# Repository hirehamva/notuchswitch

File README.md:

# No-Touch Door and Light Switch

A compact ATtiny3216 controller that switches one LED lamp by hand gesture or
when a sliding door moves in front of an APDS-9960 sensor. The repository
contains the KiCad design, parts list, PCB fabrication files, firmware, and the
documents needed to assemble and program the prototype.

## Prototype

*Controller PCB fitted in the enclosure with its cover removed.*

*Enclosure interior showing the power supply and wiring.*

*Front cover with separate sensor and status LED openings.*

## Build and program

1. Open `hardware/notuchswitch.kicad_pro` in KiCad 9 or later. PCB component
   placement is fixed; use the supplied Gerbers to order the board.
2. Assemble the board using [`hardware/BOM.csv`](hardware/BOM.csv) and the
   [hardware notes](hardware/README.md). Confirm the parts marked for footprint
   verification before ordering or soldering.
3. Open `software/notuchswitch_firmware/notuchswitch_firmware.ino` in Arduino
   IDE 2. Install megaTinyCore and select the ATtiny3216 settings described in
   [`software/README.md`](software/README.md).
4. Program through the on-board J7 SerialUPDI header using a 3.3 V USB-to-UART
   adapter. The classic USBasp programmer does not connect directly to J7; see
   [`software/SERIALUPDI.md`](software/SERIALUPDI.md).
5. Print the [cover drilling template](hardware/templates/cover_drill_template.pdf)
   at 100% and verify its 20 mm scale bar before drilling.

See the [user guide](docs/user-guide.md) for operation, menu settings, and
calibration.

## Safety and license

This is a mains-powered engineering prototype, not a certified product. Verify
the exact components, insulation distances, enclosure, wiring, temperature,
and applicable electrical safety requirements before connecting it to mains.

The project is released under the MIT License; see [`LICENSE`](LICENSE).

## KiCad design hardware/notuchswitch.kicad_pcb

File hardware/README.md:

# Hardware Assembly

Open `notuchswitch.kicad_pro` in KiCad 9 or later. The PCB placement and
outline are fixed to fit the selected enclosure; do not move components.

## Required files

- `notuchswitch.kicad_sch`, `notuchswitch.kicad_pcb`, and
  `notuchswitch.kicad_pro`: schematic, PCB, and project.
- `BOM.csv`: component values, footprints, and parts that still need a
  dimensional check.
- `fabrication/gerber/`: copper, mask, silkscreen, outline, and drill files
  for PCB fabrication.
- `notuchswitch.pretty/`, `notuchswitch.kicad_sym`, `fp-lib-table`, and
  `sym-lib-table`: project-local footprints and symbol library configuration.
- `templates/cover_drill_template.pdf`: printable sensor and LED hole layout.

## Assembly notes

1. Order the PCB from the supplied Gerber and drill files, or export fresh
   fabrication files from the reviewed KiCad project.
2. Populate components according to `BOM.csv`. The fuse, varistor, and X2
   capacitor footprints are placeholders: verify the exact purchased parts,
   lead spacing, and body dimensions before soldering.
3. Confirm the APDS-9960 breakout pin order before inserting it. The board
   expects `VL, GND, VCC, SDA, SCL, INT`.
4. Solder the four marked 0.75 mm2 leads: brown `L_IN`, blue `N_IN`, black
   `L_SW`, and blue `N_OUT`. Keep the two neutral leads separately identified.
5. Relay pin 14 is brought out to solder pad `J8`. Connect it to fused live
   with an insulated external wire as shown by the schematic.
6. Do not tin stranded wire ends that will be clamped into screw terminals.
7. Mount the enclosure first, then fit the PCB. Print the cover template at
   100% and verify its 20 mm scale bar before drilling.

## Design details

- Two-layer, 1.0 mm FR4 PCB with a fixed octagonal outline.
- `HLK-2M05` isolated supply: 5 V, 400 mA continuous. Verify the load budget
  for the relay, LED, and the exact APDS breakout used.
- The recommended `10D561K` varistor may not match the supplied substitute;
  confirm its rating and dimensions against the supply manufacturer's data.
- Mains and low-voltage copper are separated by the project's 3 mm design rule.
- J7 is the on-board 2x2 SerialUPDI interface. R9 (470 ohm) and D5 (BAT54HT1G)
  are already fitted on the PCB design.
- USB-A provides 5 V only; D+ and D- are unconnected. Charging behavior is
  device-dependent and is not guaranteed.

The Gerber set is included as a fabrication artifact. Recheck the current KiCad
design, exact purchased components, and electrical safety before fabrication or
connecting mains. This prototype is not a certified product.

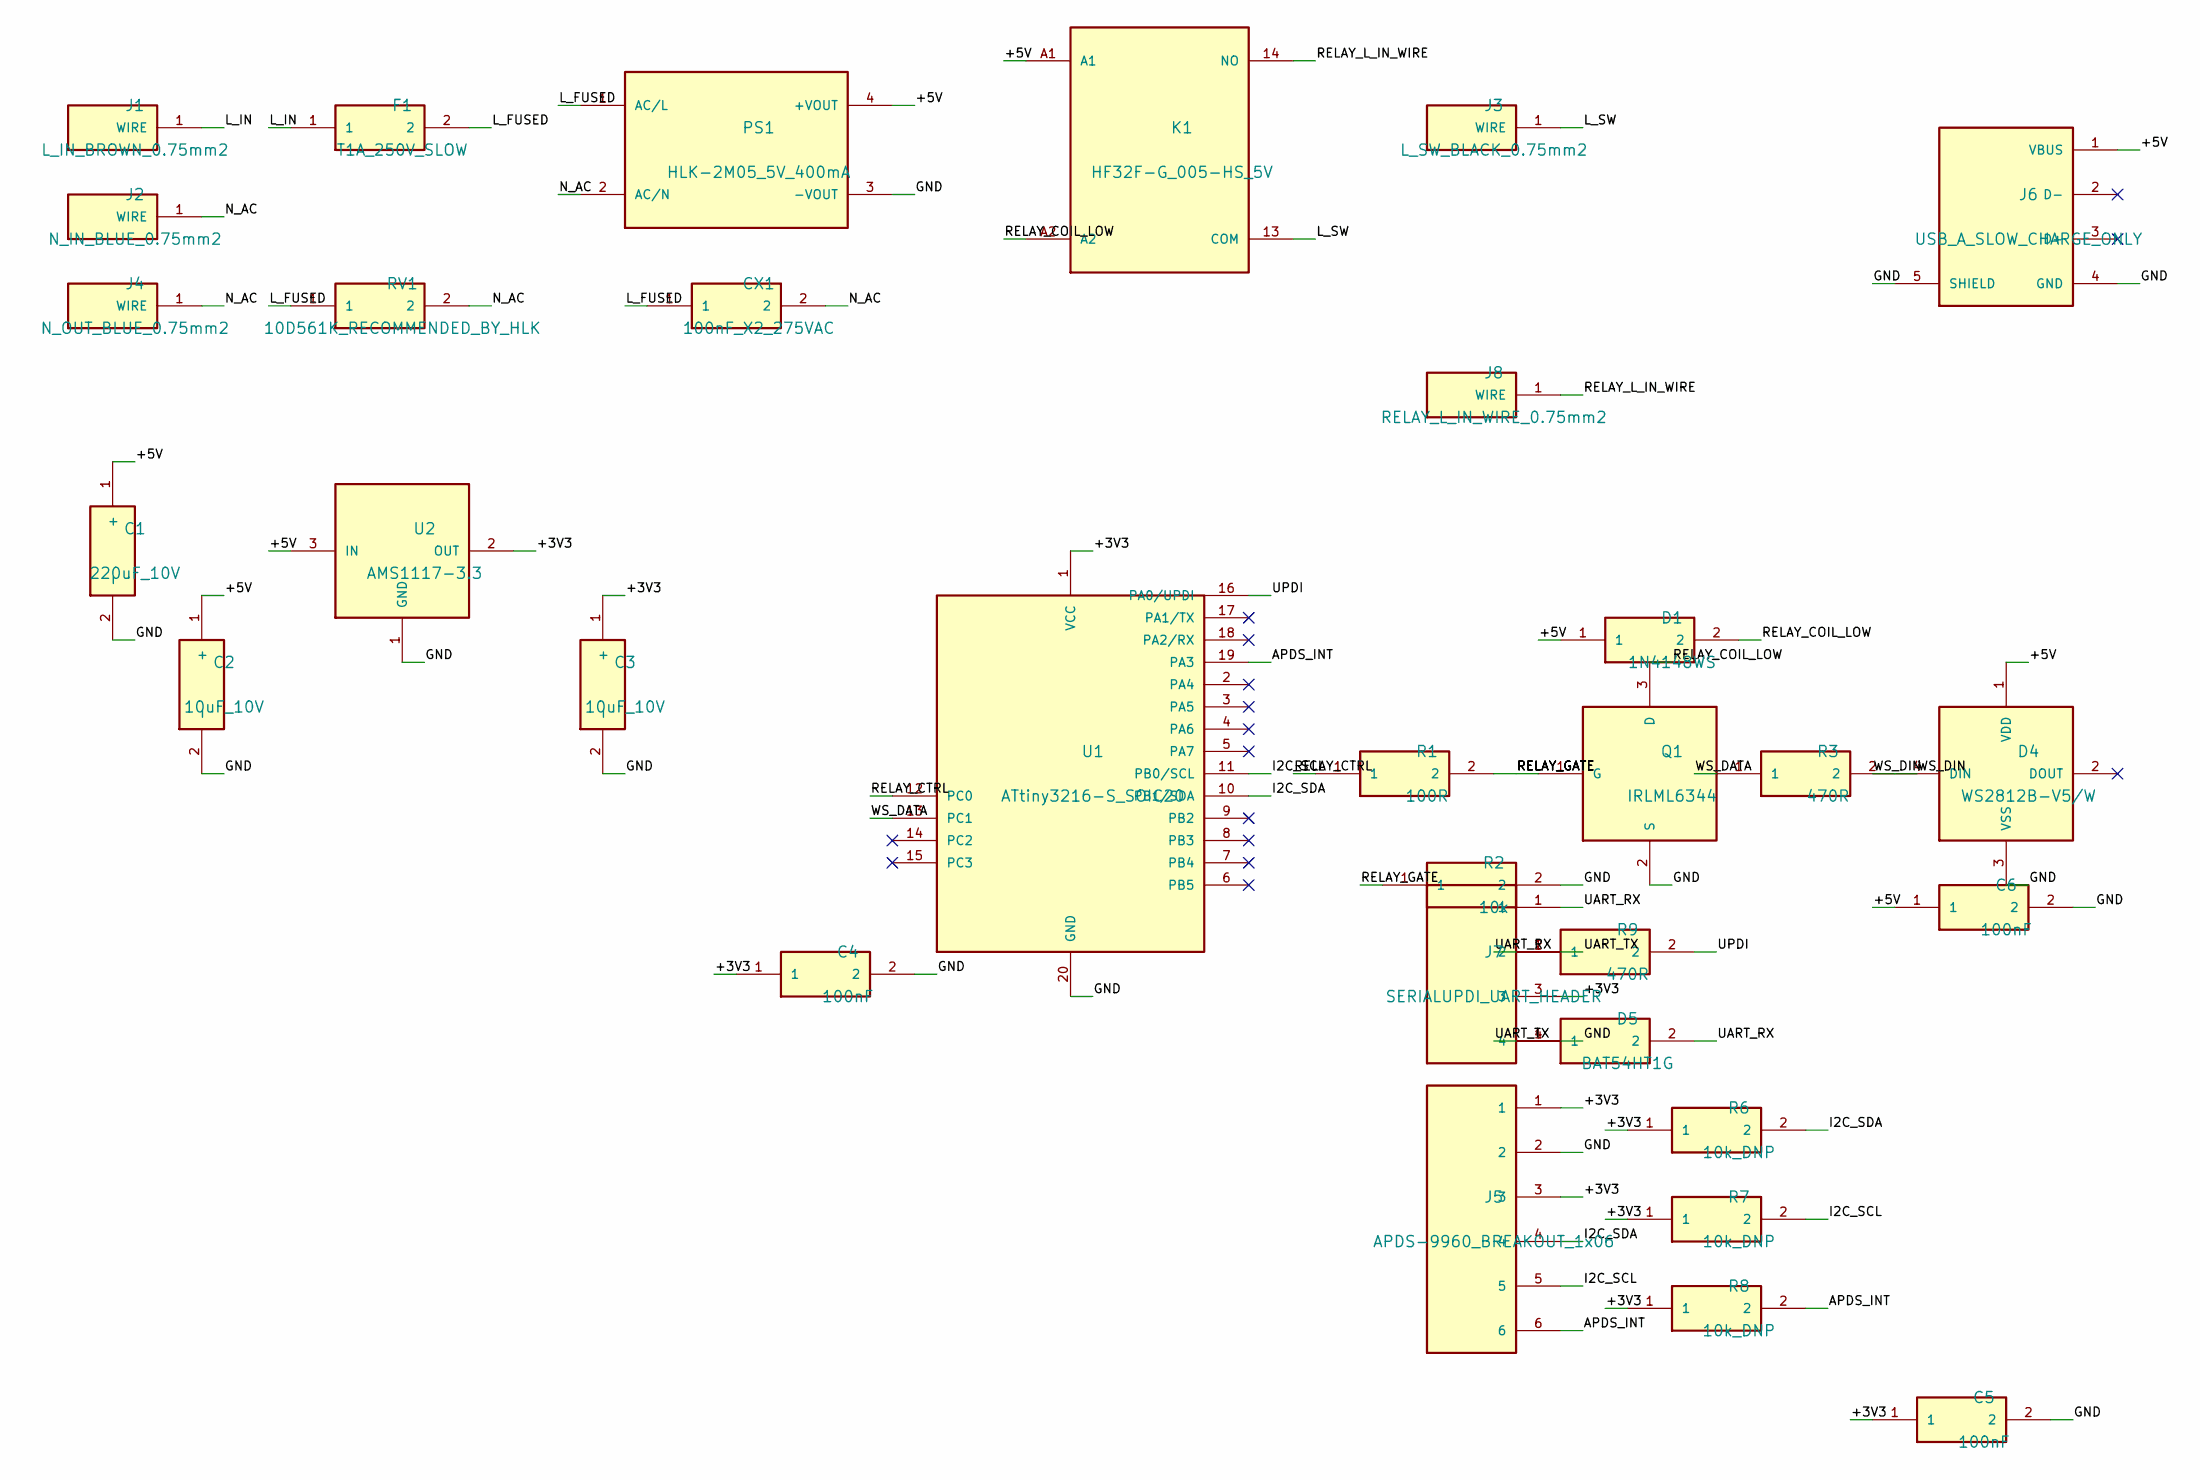
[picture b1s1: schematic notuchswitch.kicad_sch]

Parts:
C1: 220uF_10V; C_Radial_D6.3mm_H7.0mm_P2.50mm
C2, C3: 10uF_10V; C_Radial_D5.0mm_H5.0mm_P2.00mm
C4, C5, C6: 100nF; C_0805_2012Metric_Pad1.18x1.45mm_HandSolder
CX1: 100nF_X2_275VAC; X2_Capacitor_P10.00mm_PLACEHOLDER
D1: 1N4148WS; D_SOD-323_HandSoldering
D4: WS2812B-V5/W; LED_WS2812B_PLCC4_5.0x5.0mm_P3.2mm
D5: BAT54HT1G; D_SOD-323_HandSoldering
F1: T1A_250V_SLOW; Fuse_Radial_P5.08mm_PLACEHOLDER
J1: L_IN_BROWN_0.75mm2; WirePad_D3.2mm
J2: N_IN_BLUE_0.75mm2; WirePad_D3.2mm
J3: L_SW_BLACK_0.75mm2; WirePad_D3.2mm
J4: N_OUT_BLUE_0.75mm2; WirePad_D3.2mm
J5: APDS-9960_BREAKOUT_1x06; PinHeader_1x06_P2.54mm_Vertical
J6: USB_A_SLOW_CHARGE_ONLY; USB_A_Molex_67643_Horizontal
J7: SERIALUPDI_UART_HEADER; PinHeader_2x02_P2.54mm_Vertical
J8: RELAY_L_IN_WIRE_0.75mm2; WirePad_D3.2mm
K1: HF32F-G_005-HS_5V; HF32F-G
PS1: HLK-2M05_5V_400mA; HLK-2M05
Q1: IRLML6344; SOT-23
R1: 100R; R_0805_2012Metric_Pad1.20x1.40mm_HandSolder
R2: 10k; R_0805_2012Metric_Pad1.20x1.40mm_HandSolder
R3, R9: 470R; R_0805_2012Metric_Pad1.20x1.40mm_HandSolder
R6, R7, R8: 10k_DNP; R_0805_2012Metric_Pad1.20x1.40mm_HandSolder
RV1: 10D561K_RECOMMENDED_BY_HLK; Varistor_10D_P7.50mm_PLACEHOLDER
U1: ATtiny3216-S_SOIC20; SOIC-20W_7.5x12.8mm_P1.27mm
U2: AMS1117-3.3; SOT-223-3_TabPin2

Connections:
+3V3: C3.1 (+), C4.1, C5.1, J5.1, J5.3, J7.3, R6.1, R7.1, R8.1, U1.1 (VCC), U2.2 (OUT)
+5V: C1.1 (+), C2.1 (+), C6.1, D1.1, D4.1 (VDD), J6.1 (VBUS), K1.A1, PS1.4 (+VOUT), U2.3 (IN)
APDS_INT: J5.6, R8.2, U1.19 (PA3)
GND: C1.2 (-), C2.2 (-), C3.2 (-), C4.2, C5.2, C6.2, D4.3 (VSS), J5.2, J6.4 (GND), J6.5 (SHIELD), J7.4, PS1.3 (-VOUT), Q1.2 (S), R2.2, U1.20 (GND), U2.1 (GND)
I2C_SCL: J5.5, R7.2, U1.11 (PB0/SCL)
I2C_SDA: J5.4, R6.2, U1.10 (PB1/SDA)
L_FUSED: CX1.1, F1.2, PS1.1 (AC/L), RV1.1
L_IN: F1.1, J1.1
L_SW: J3.1, K1.13 (COM)
N_AC: CX1.2, J2.1, J4.1, PS1.2 (AC/N), RV1.2
RELAY_COIL_LOW: D1.2, K1.A2, Q1.3 (D)
RELAY_CTRL: R1.1, U1.12 (PC0)
RELAY_GATE: Q1.1 (G), R1.2, R2.1
RELAY_L_IN_WIRE: J8.1, K1.14 (NO)
UART_RX: D5.2, J7.1, R9.1
UART_TX: D5.1, J7.2
UPDI: R9.2, U1.16 (PA0/UPDI)
WS_DATA: R3.1, U1.13 (PC1)
WS_DIN: D4.4 (DIN), R3.2

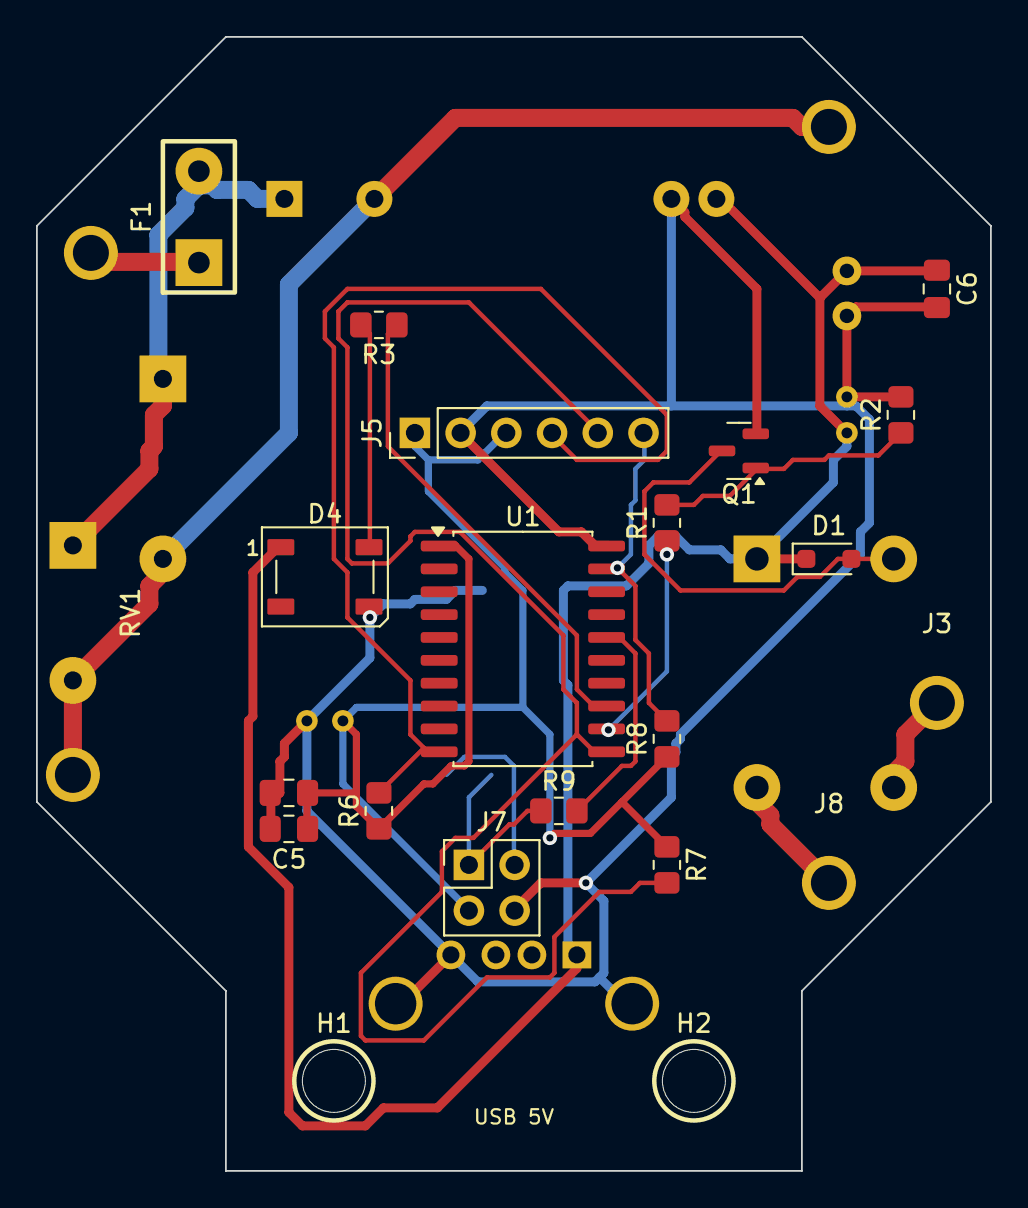
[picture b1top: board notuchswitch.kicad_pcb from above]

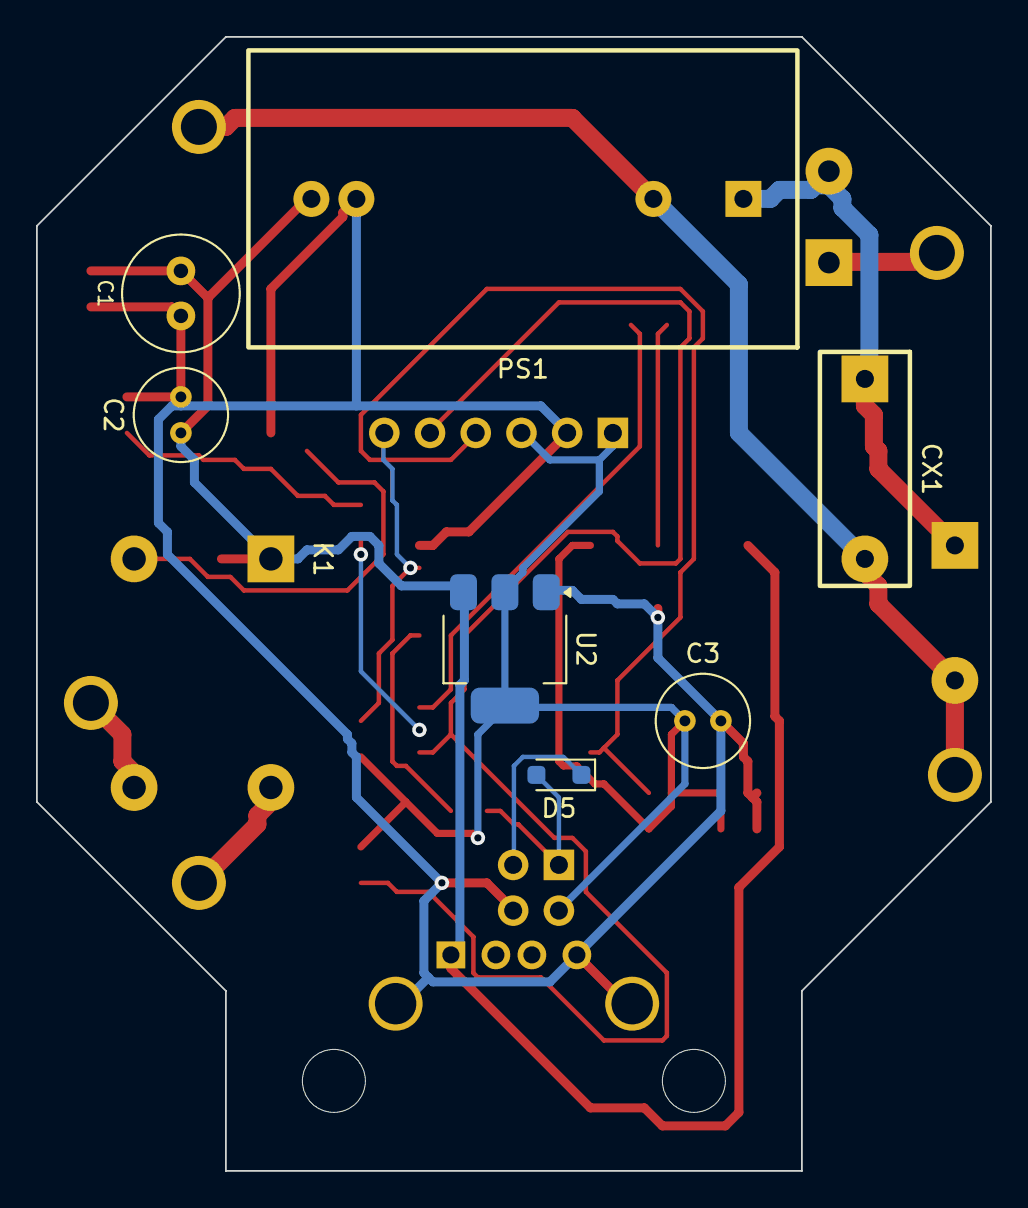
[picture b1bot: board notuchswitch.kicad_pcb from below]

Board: 2 copper layers, 53.0 x 63.0 mm, 34 parts (9 on the bottom side), 19 nets.

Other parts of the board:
H1, H2: MountingHole_3.5mm

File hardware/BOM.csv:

Reference,Value,Footprint,Status,Note
J1,L_IN_BROWN_0.75mm2,notuchswitch:WirePad_D3.2mm,selected,Soldered brown mains lead
J2,N_IN_BLUE_0.75mm2,notuchswitch:WirePad_D3.2mm,selected,Soldered blue neutral input lead
J3,L_SW_BLACK_0.75mm2,notuchswitch:WirePad_D3.2mm,selected,Soldered black switched-live output lead
J4,N_OUT_BLUE_0.75mm2,notuchswitch:WirePad_D3.2mm,selected,Soldered blue neutral onward lead; mark separately from J2
J8,RELAY_L_IN_WIRE_0.75mm2,notuchswitch:WirePad_D3.2mm,selected,Relay pin 14 solder pad; connect to fused live with an external insulated wire
F1,T1A_250V_SLOW,notuchswitch:Fuse_Radial_P5.08mm_PLACEHOLDER,verify footprint,Soldered PCB fuse; verify purchased fuse dimensions
RV1,10D561K_RECOMMENDED_BY_HLK,notuchswitch:Varistor_10D_P7.50mm_PLACEHOLDER,verify footprint,"THT varistor; HLK-2M05 datasheet recommends 10D561K, verify exact purchased part and spacing"
CX1,100nF_X2_275VAC,notuchswitch:X2_Capacitor_P10.00mm_PLACEHOLDER,verify footprint,THT class X2 capacitor; verify exact body dimensions
PS1,HLK-2M05_5V_400mA,notuchswitch:HLK-2M05,selected,"Selected isolated AC/DC module, 30.5 x 16.5 x 19 mm body; 400 mA continuous, at least 500 mA short-term"
K1,HF32F-G_005-HS_5V,notuchswitch:HF32F-G,selected,Normally-open relay: hardware default is OFF; pin 14 is fed through J8 by an external insulated wire
C1,220uF_10V,Capacitor_THT:C_Radial_D6.3mm_H7.0mm_P2.50mm,selected,5 V output bulk capacitor
U2,AMS1117-3.3,Package_TO_SOT_SMD:SOT-223-3_TabPin2,selected,
C2,10uF_10V,Capacitor_THT:C_Radial_D5.0mm_H5.0mm_P2.00mm,selected,AMS1117 input capacitor
C3,10uF_10V,Capacitor_THT:C_Radial_D5.0mm_H5.0mm_P2.00mm,selected,AMS1117 output capacitor
C4,100nF,Capacitor_SMD:C_0805_2012Metric_Pad1.18x1.45mm_HandSolder,selected,MCU local decoupling
C5,100nF,Capacitor_SMD:C_0805_2012Metric_Pad1.18x1.45mm_HandSolder,selected,APDS module local decoupling
C6,100nF,Capacitor_SMD:C_0805_2012Metric_Pad1.18x1.45mm_HandSolder,selected,WS2812 local decoupling
U1,ATtiny3216-S_SOIC20,Package_SO:SOIC-20W_7.5x12.8mm_P1.27mm,selected,Official KiCad ATtiny3216-S pinout checked; unused GPIO remain free
Q1,IRLML6344,Package_TO_SOT_SMD:SOT-23,selected,
D1,1N4148WS,Diode_SMD:D_SOD-323_HandSoldering,selected,Relay flyback diode: pin 1 cathode to +5 V
D5,BAT54HT1G,Diode_SMD:D_SOD-323_HandSoldering,selected,SerialUPDI Schottky diode: pin 1 cathode to UART_TX
R1,100R,Resistor_SMD:R_0805_2012Metric_Pad1.20x1.40mm_HandSolder,selected,
R2,10k,Resistor_SMD:R_0805_2012Metric_Pad1.20x1.40mm_HandSolder,selected,MOSFET gate pull-down keeps relay OFF at reset
J5,APDS-9960_BREAKOUT_1x06,Connector_PinHeader_2.54mm:PinHeader_1x06_P2.54mm_Vertical,verify module pin order,"Expected order VL,GND,VCC,SDA,SCL,INT; verify delivered breakout before soldering"
R6,10k_DNP,Resistor_SMD:R_0805_2012Metric_Pad1.20x1.40mm_HandSolder,DNP optional,Optional SDA pull-up
R7,10k_DNP,Resistor_SMD:R_0805_2012Metric_Pad1.20x1.40mm_HandSolder,DNP optional,Optional SCL pull-up
R8,10k_DNP,Resistor_SMD:R_0805_2012Metric_Pad1.20x1.40mm_HandSolder,DNP optional,Optional INT pull-up
D4,WS2812B-V5/W,LED_SMD:LED_WS2812B_PLCC4_5.0x5.0mm_P3.2mm,selected,V5/W VIH margin is narrow at 3.3 V MCU drive; verify on prototype
R3,470R,Resistor_SMD:R_0805_2012Metric_Pad1.20x1.40mm_HandSolder,selected,
R9,470R,Resistor_SMD:R_0805_2012Metric_Pad1.20x1.40mm_HandSolder,selected,On-board SerialUPDI series resistor
J6,USB_A_SLOW_CHARGE_ONLY,Connector_USB:USB_A_Molex_67643_Horizontal,selected,Direct +5 V VBUS; D+/D- intentionally unconnected; charging speed and phone compatibility are device-dependent
J7,SERIALUPDI_UART_HEADER,Connector_PinHeader_2.54mm:PinHeader_2x02_P2.54mm_Vertical,selected,Compact 2x2 2.54 mm header for direct USB-UART module connection
